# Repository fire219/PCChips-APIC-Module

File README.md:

# PCChips APIC Module
### Make your M720 slightly less useless!

The [PCChips M720](https://theretroweb.com/motherboards/s/pcchips-m720) is a dual [Slot 1](https://en.wikipedia.org/wiki/Slot_1) motherboard that doesn't necessarily run dual CPUs.

In all their cost-cutting wisdom, a needed component was left off the board -- the Intel 82093AA [APIC](https://en.wikipedia.org/wiki/Advanced_Programmable_Interrupt_Controller), which handles interrupt routing between multiple processors. Instead, they added a card slot for a module that houses the APIC. Without it, the M720 is just an incredibly mediocre Slot 1 motherboard. And in the modern day, most of the examples you find for sale don't have the module included.

If you're one of those poor souls to have a module-less M720, here's your chance to fix that.

This is a re-engineered module that should fit in the existing slot, with a few changes made to make it easier to hand-solder together. All that you need is:

* This PCB ([JLCPCB can fab it for cheap](https://jlcpcb.com/))
* The S82093AA APIC (check eBay or Aliexpress)
* 4x 4.7kΩ resistors (1206 size)
* 4x 100nF capacitors (1206 size)

#### Compatible boards:
* PCChips M720
* PCChips M720II
* Amptron PII-2200A
* Amptron PII-2200B
* Alton ALTN-7020
* PC Ware MB-720
* EURONE EM-7020

#### License:

    Copyright (c) 2023 Matthew Petry (fireTwoOneNine)
    
    Permission is hereby granted, free of charge, to any person obtaining a copy
    of this software and associated documentation files (the "Software"), to deal
    in the Software without restriction, including without limitation the rights
    to use, copy, modify, merge, publish, distribute, sublicense, and/or sell
    copies of the Software, and to permit persons to whom the Software is
    furnished to do so, subject to the following conditions:
    
    The above copyright notice and this permission notice shall be included in all
    copies or substantial portions of the Software.
    
    THE SOFTWARE IS PROVIDED "AS IS", WITHOUT WARRANTY OF ANY KIND, EXPRESS OR
    IMPLIED, INCLUDING BUT NOT LIMITED TO THE WARRANTIES OF MERCHANTABILITY,
    FITNESS FOR A PARTICULAR PURPOSE AND NONINFRINGEMENT. IN NO EVENT SHALL THE
    AUTHORS OR COPYRIGHT HOLDERS BE LIABLE FOR ANY CLAIM, DAMAGES OR OTHER
    LIABILITY, WHETHER IN AN ACTION OF CONTRACT, TORT OR OTHERWISE, ARISING FROM,
    OUT OF OR IN CONNECTION WITH THE SOFTWARE OR THE USE OR OTHER DEALINGS IN THE
    SOFTWARE.

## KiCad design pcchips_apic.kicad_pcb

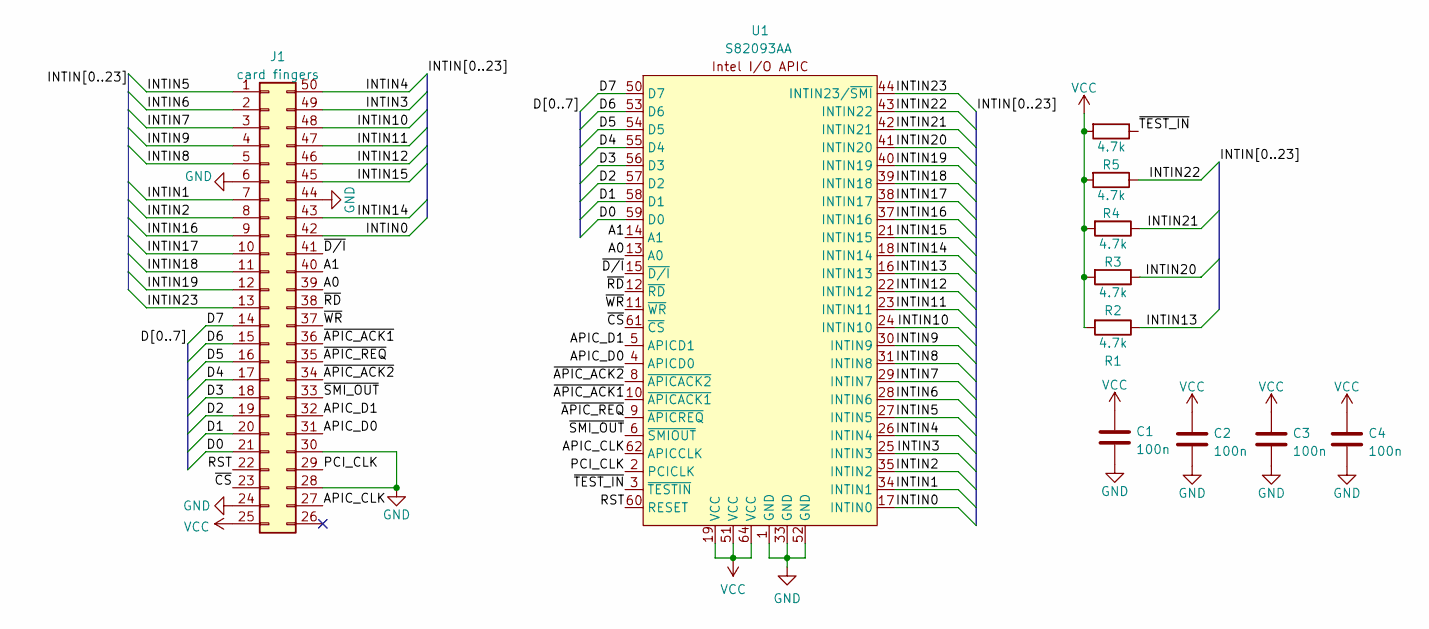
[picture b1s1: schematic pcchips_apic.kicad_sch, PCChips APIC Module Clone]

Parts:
C1, C2, C3, C4: 100n; C_1206_3216Metric_Pad1.33x1.80mm_HandSolder
J1: card fingers; APIC_module_fingers
R1, R2, R3, R4, R5: 4.7k; R_1206_3216Metric_Pad1.30x1.75mm_HandSolder
U1: S82093AA; QFP64-14x20mm

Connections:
/A0: J1.39, U1.13 (A0); also elsewhere on the board
/A1: J1.40, U1.14 (A1); also elsewhere on the board
/APIC_CLK: J1.27, U1.62 (APICCLK); also elsewhere on the board
/APIC_D0: J1.31, U1.4 (APICD0); also elsewhere on the board
/APIC_D1: J1.32, U1.5 (APICD1); also elsewhere on the board
/D0: J1.21, U1.59 (D0); also elsewhere on the board
/D1: J1.20, U1.58 (D1); also elsewhere on the board
/D2: J1.19, U1.57 (D2); also elsewhere on the board
/D3: J1.18, U1.56 (D3); also elsewhere on the board
/D4: J1.17, U1.55 (D4); also elsewhere on the board
/D5: J1.16, U1.54 (D5); also elsewhere on the board
/D6: J1.15, U1.53 (D6); also elsewhere on the board
/D7: J1.14, U1.50 (D7); also elsewhere on the board
/INTIN0: J1.42, U1.17 (INTIN0); also elsewhere on the board
/INTIN1: J1.7, U1.34 (INTIN1); also elsewhere on the board
/INTIN2: J1.8, U1.35 (INTIN2); also elsewhere on the board
/INTIN3: J1.49, U1.25 (INTIN3); also elsewhere on the board
/INTIN4: J1.50, U1.26 (INTIN4); also elsewhere on the board
/INTIN5: J1.1, U1.27 (INTIN5); also elsewhere on the board
/INTIN6: J1.2, U1.28 (INTIN6); also elsewhere on the board
/INTIN7: J1.3, U1.29 (INTIN7); also elsewhere on the board
/INTIN8: J1.5, U1.31 (INTIN8); also elsewhere on the board
/INTIN9: J1.4, U1.30 (INTIN9); also elsewhere on the board
/INTIN10: J1.48, U1.24 (INTIN10); also elsewhere on the board
/INTIN11: J1.47, U1.23 (INTIN11); also elsewhere on the board
/INTIN12: J1.46, U1.22 (INTIN12); also elsewhere on the board
/INTIN13: R1.1, U1.16 (INTIN13)
/INTIN14: J1.43, U1.18 (INTIN14); also elsewhere on the board
/INTIN15: J1.45, U1.21 (INTIN15); also elsewhere on the board
/INTIN16: J1.9, U1.37 (INTIN16); also elsewhere on the board
/INTIN17: J1.10, U1.38 (INTIN17); also elsewhere on the board
/INTIN18: J1.11, U1.39 (INTIN18); also elsewhere on the board
/INTIN19: J1.12, U1.40 (INTIN19); also elsewhere on the board
/INTIN20: R2.1, U1.41 (INTIN20)
/INTIN21: R3.1, U1.42 (INTIN21)
/INTIN22: R4.1, U1.43 (INTIN22)
/INTIN23: J1.13, U1.44 (INTIN23/~SMI); also elsewhere on the board
/PCI_CLK: J1.29, U1.2 (PCICLK); also elsewhere on the board
/RST: J1.22, U1.60 (RESET); also elsewhere on the board
/~APIC_ACK1: J1.36, U1.10 (~APICACK1); also elsewhere on the board
/~APIC_ACK2: J1.34, U1.8 (~APICACK2); also elsewhere on the board
/~APIC_REQ: J1.35, U1.9 (~APICREQ); also elsewhere on the board
/~CS: J1.23, U1.61 (~CS); also elsewhere on the board
/~D/I: J1.41, U1.15 (~D/I); also elsewhere on the board
/~RD: J1.38, U1.12 (~RD); also elsewhere on the board
/~SMI_OUT: J1.33, U1.6 (~SMIOUT); also elsewhere on the board
/~TEST_IN: R5.1, U1.3 (~TESTIN)
/~WR: J1.37, U1.11 (~WR); also elsewhere on the board
GND: C1.2, C2.2, C3.2, C4.2, J1.6, J1.24, J1.28, J1.30, J1.44, U1.1 (GND), U1.33 (GND), U1.52 (GND); also elsewhere on the board
VCC: C1.1, C2.1, C3.1, C4.1, J1.25, R1.2, R2.2, R3.2, R4.2, R5.2, U1.19 (VCC), U1.51 (VCC), U1.64 (VCC); also elsewhere on the board

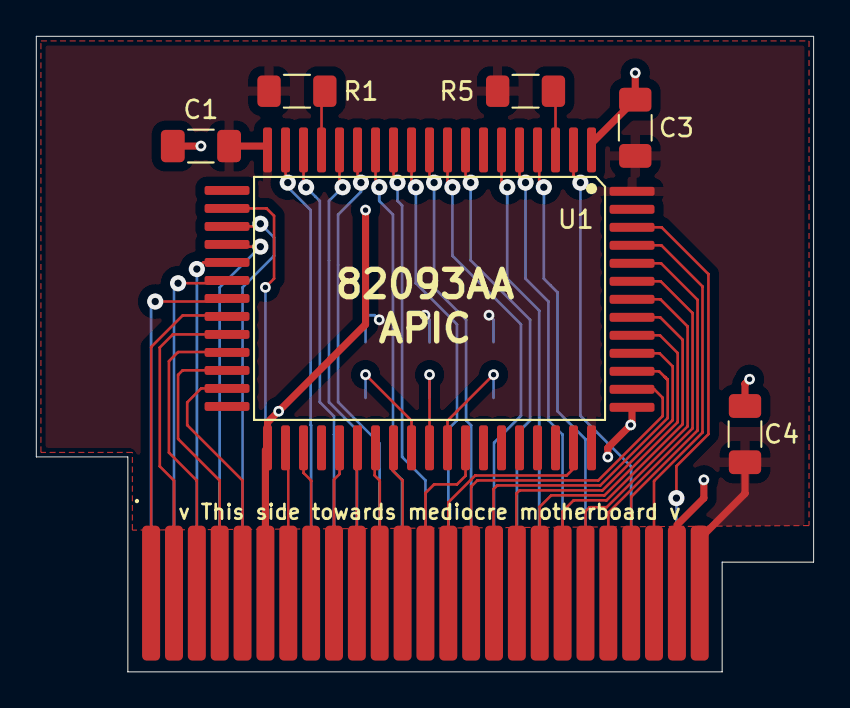
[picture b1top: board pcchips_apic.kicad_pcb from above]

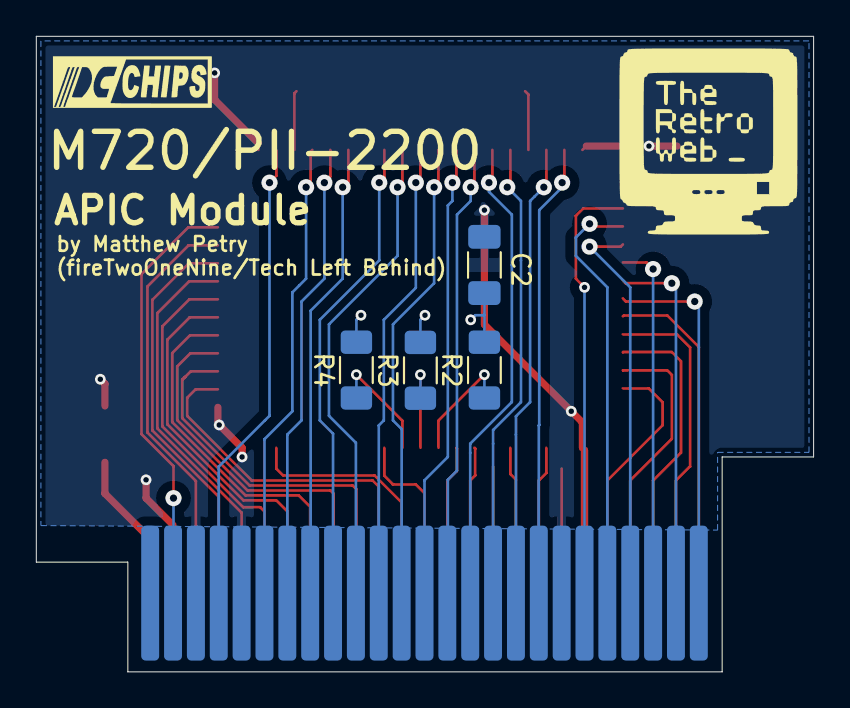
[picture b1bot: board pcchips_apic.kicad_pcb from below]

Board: 2 copper layers, 43.2 x 35.3 mm, 13 parts (6 on the bottom side), 50 nets.

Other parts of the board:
.: card fingers; APIC_module_fingers
.#2: LOGO; pcchips
.#3: LOGO; TRW_logo

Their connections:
/A0: ..39; also elsewhere on the board
/A1: ..40; also elsewhere on the board
/APIC_CLK: ..27; also elsewhere on the board
/APIC_D0: ..31; also elsewhere on the board
/APIC_D1: ..32; also elsewhere on the board
/D0: ..21; also elsewhere on the board
/D1: ..20; also elsewhere on the board
/D2: ..19; also elsewhere on the board
/D3: ..18; also elsewhere on the board
/D4: ..17; also elsewhere on the board
/D5: ..16; also elsewhere on the board
/D6: ..15; also elsewhere on the board
/D7: ..14; also elsewhere on the board
/INTIN0: ..42; also elsewhere on the board
/INTIN1: ..7; also elsewhere on the board
/INTIN2: ..8; also elsewhere on the board
/INTIN3: ..49; also elsewhere on the board
/INTIN4: ..50; also elsewhere on the board
/INTIN5: ..1; also elsewhere on the board
/INTIN6: ..2; also elsewhere on the board
/INTIN7: ..3; also elsewhere on the board
/INTIN8: ..5; also elsewhere on the board
/INTIN9: ..4; also elsewhere on the board
/INTIN10: ..48; also elsewhere on the board
/INTIN11: ..47; also elsewhere on the board
/INTIN12: ..46; also elsewhere on the board
/INTIN14: ..43; also elsewhere on the board
/INTIN15: ..45; also elsewhere on the board
/INTIN16: ..9; also elsewhere on the board
/INTIN17: ..10; also elsewhere on the board
/INTIN18: ..11; also elsewhere on the board
/INTIN19: ..12; also elsewhere on the board
/INTIN23: ..13; also elsewhere on the board
/PCI_CLK: ..29; also elsewhere on the board
/RST: ..22; also elsewhere on the board
/~APIC_ACK1: ..36; also elsewhere on the board
/~APIC_ACK2: ..34; also elsewhere on the board
/~APIC_REQ: ..35; also elsewhere on the board
/~CS: ..23; also elsewhere on the board
/~D/I: ..41; also elsewhere on the board
/~RD: ..38; also elsewhere on the board
/~SMI_OUT: ..33; also elsewhere on the board
/~WR: ..37; also elsewhere on the board
GND: ..6, ..24, ..28, ..30, ..44; also elsewhere on the board
VCC: ..25; also elsewhere on the board
